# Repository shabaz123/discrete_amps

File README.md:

# Discrete Amps

This repository contains  discrete audio amplifier designs intended primarily for speech applications (speech bandwidth, not music).  

Each design includes:
- KiCad 10 Schematic and PCB files
- KiCad 10 SPICE Simulation Workbook
- Gerber files for fabrication  
- PDF schematic export and PCB screenshots for easy viewing without KiCad  

---

## Preamp K1

Designed by M. Kellett, this preamplifier is optimised for speech signals in HF receivers.

- **Gain:** ~28 dB  
- **Bandwidth (-3 dB):** ~150 Hz to 10 kHz (approximate)  
- **Use case:** Moderate gain front-end with relatively wide speech bandwidth  

### Schematic

### PCB Top

### PCB Underside

### PCB Render

---

## Preamp K2

Also designed by M. Kellett, this version provides higher gain and a slightly narrower bandwidth, making it suitable where additional amplification is required.

- **Gain:** ~45 dB  
- **Bandwidth (-3 dB):** ~100 Hz to 7 kHz (approximate)  
- **Use case:** Higher gain stage for weak signal amplification  

### Schematic

### PCB Top

### PCB Underside

### PCB Render

---

## Poweramp K1

Also designed by M. Kellett, this amplifier is a power stage, and it directly drives 8 ohm speakers, with low distortion (less than 0.5%) at 280 mW.

- **Gain:** ~27 dB  
- **Bandwidth (-3 dB):** ~50 Hz to 30 kHz (approximate)  
- **Use case:** Driving an 8-ohm speaker in a radio receiver  

### Schematic

### PCB Top

### PCB Underside

### PCB Render

---

## Diffamp S1

This is a difference amplifier, designed for input signals up to about 400 mV p-p. Note: this circuit has not been assembled yet, and may have instabilities. 

- **Gain:** ~10 dB  
- **Bandwidth (-3 dB):** ~30 Hz to 40 kHz (approximate)  
- **Use case:** Acting somewhat like a telephone hybrid, for a DIY intercom/field phone, to remove the local audio sound from the remotely received sound

Note: For higher gain (about 30 dB) and correspondingly lower maximum imput signals, make the following two changes:

1. Take the output from Q4 collector, rather than Q3 collector
2. Move C6 to Q4 collector instead of Q3 collector.

### Schematic

### PCB Top

### PCB Underside

### PCB Render

---

## Notes

These designs are intended for experimentation and adaptation.

All components are easy to source. 

For the 9V power connection, the PCB will accomodate any 2-pin screw terminal block with 3.5 to 5.08 mm pin pitch. 

For the audio input and output, an AliExpress stereo audio jack socket can be used (only the tip and the screen is used, the ring is not connected). Alternatively, the audio connections can be made with 0.1" pin headers (they will fit in the same footprint, as there are extra holes for that). 

The potentiometer can be ALPS RK097 series (available from AliExpress), it has pins at 2.5 mm pitch, and a body width of 10 mm.

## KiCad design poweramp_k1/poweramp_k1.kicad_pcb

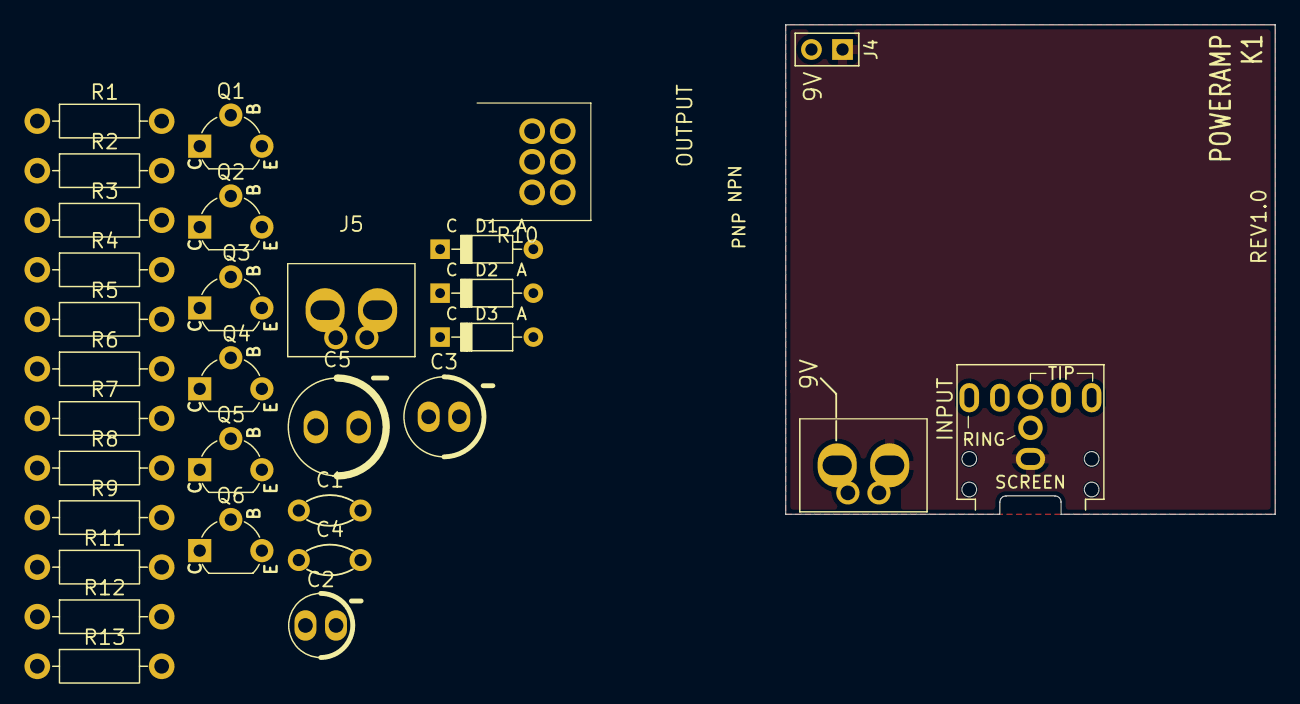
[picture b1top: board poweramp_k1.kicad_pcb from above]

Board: 2 copper layers, 40.0 x 40.0 mm, 31 parts (0 on the bottom side), 20 nets, no tracks yet.

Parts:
C1: 220n; C_Disc_T3.0mm_P5.0
C2: 10u; CP_Radial_D5.0mm_P2.50mm
C3: 47u; CP_Radial_D6.3mm_P2.50mm
C4: 270p; C_Disc_T3.0mm_P5.0
C5: 470u; CP_Radial_D8mm_P3.5mm
D1, D2, D3: 1N4148; Diode-DO-35_1.75mmDia_3.4mmWidth_P7.62mm
J1: AudioJack_Stereo; Jack_3.5mm_CUI_SJ1-3525N_Horizontal
J3: 9VDC; TerminalBlock_2way-3.5-5.0mm
J4: PinHeader_1x02_P2.54mm_Vertical
J5: SPEAKER; TerminalBlock_2way-3.5-5.0mm
Q1, Q5, Q6: BC547; BJT_NPN_BC547
Q2: BC337-25; BJT_NPN_BC547
Q3: BC557; BJT_PNP_BC557
Q4: BC327-25; BJT_PNP_BC557
R1, R2: 2.2R; R_Axial_L6.3mm_D2.5mm_P10.16mm_Horiz
R3: 10k; R_Axial_L6.3mm_D2.5mm_P10.16mm_Horiz
R4: 1.5k; R_Axial_L6.3mm_D2.5mm_P10.16mm_Horiz
R5: 1k; R_Axial_L6.3mm_D2.5mm_P10.16mm_Horiz
R6: 33k; R_Axial_L6.3mm_D2.5mm_P10.16mm_Horiz
R7: 150R; R_Axial_L6.3mm_D2.5mm_P10.16mm_Horiz
R8: 2k; R_Axial_L6.3mm_D2.5mm_P10.16mm_Horiz
R9: 22k; R_Axial_L6.3mm_D2.5mm_P10.16mm_Horiz
R10: 22k; Potentiometer_RD701F
R11: 630R; R_Axial_L6.3mm_D2.5mm_P10.16mm_Horiz
R12: 27k; R_Axial_L6.3mm_D2.5mm_P10.16mm_Horiz
R13: 43k; R_Axial_L6.3mm_D2.5mm_P10.16mm_Horiz

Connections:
0V: C2.2, C3.2, D3.1 (K), J1.S, J3.2, J4.1, J5.2, Q4.1 (C), R4.2, R7.2, R10.1, R13.2
/IN: J1.T, R10.3
/OUT: C5.2, J5.1
unnamed: C1.1, R10.2
unnamed: C2.1, R5.2
unnamed: C3.1, R3.2, R6.1
unnamed: C4.2, C5.1, R1.2, R2.1, R9.2
unnamed: D1.2 (A), Q2.2 (B), Q3.1 (C)
unnamed: D1.1 (K), D2.2 (A)
unnamed: D2.1 (K), Q4.2 (B), Q5.1 (C)
unnamed: D3.2 (A), R8.2
unnamed: C1.2, Q1.2 (B), R6.2, R13.1
unnamed: Q1.1 (C), Q3.2 (B), R11.2
unnamed: Q1.3 (E), Q6.3 (E), R4.1
unnamed: Q2.3 (E), R1.1
unnamed: Q4.3 (E), R2.2
unnamed: Q5.2 (B), R8.1, R12.2
unnamed: Q5.3 (E), R7.1
unnamed: C4.1, Q6.2 (B), R5.1, R9.1
V+: J3.1, J4.2, Q2.1 (C), Q3.3 (E), Q6.1 (C), R3.1, R11.1, R12.1

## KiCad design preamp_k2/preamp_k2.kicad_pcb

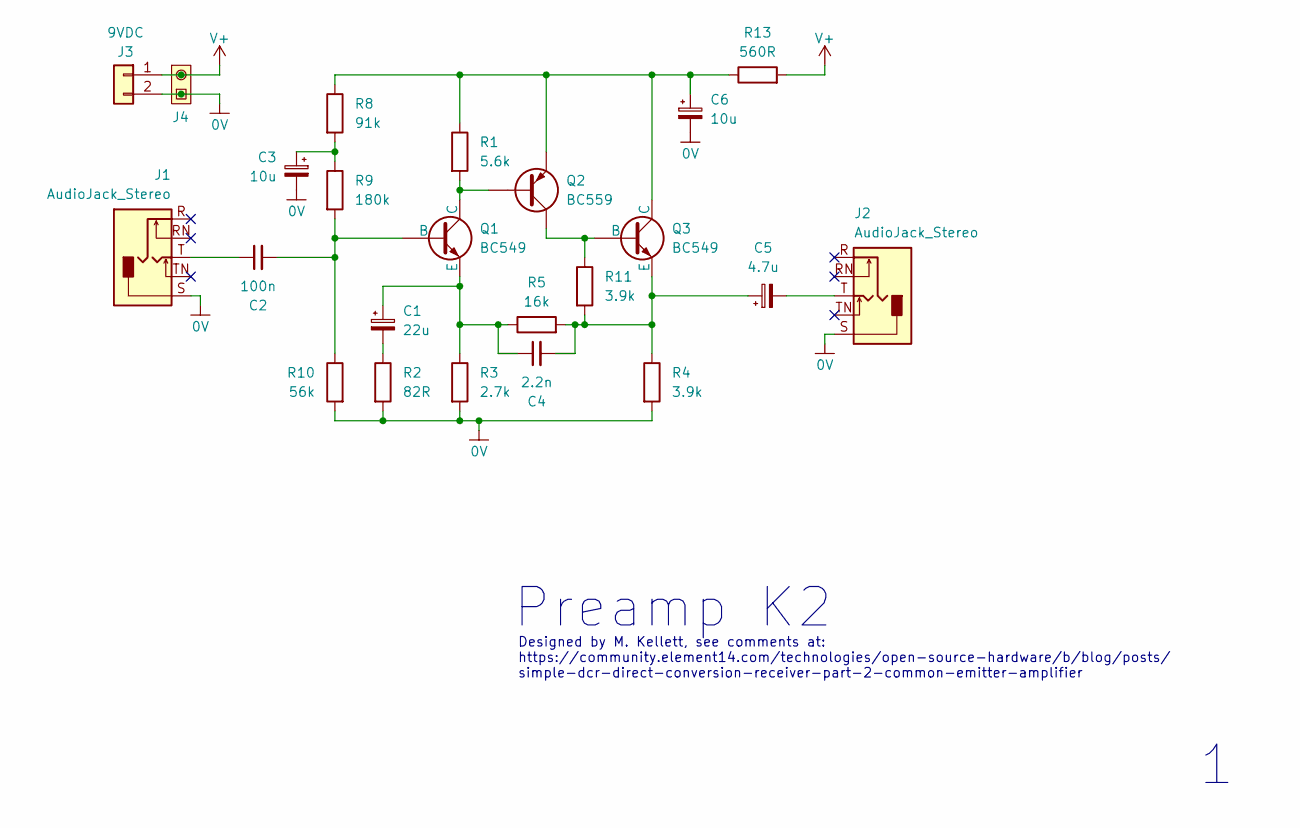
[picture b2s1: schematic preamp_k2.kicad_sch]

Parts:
C1: 22u; CP_Radial_D5.0mm_P2.50mm
C2: 100n; C_Disc_T3.0mm_P5.0
C3, C6: 10u; CP_Radial_D5.0mm_P2.50mm
C4: 2.2n; C_Disc_T3.0mm_P5.0
C5: 4.7u; CP_Radial_D5.0mm_P2.50mm
J1, J2: AudioJack_Stereo; Jack_3.5mm_CUI_SJ1-3525N_Horizontal
J3: 9VDC; TerminalBlock_2way-3.5-5.0mm
J4: PinHeader_1x02_P2.54mm_Vertical
Q1, Q3: BC549; BJT_NPN_BC547
Q2: BC559; BJT_PNP_BC557
R1: 5.6k; R_Axial_L6.3mm_D2.5mm_P10.16mm_Horiz
R2: 82R; R_Axial_L6.3mm_D2.5mm_P10.16mm_Horiz
R3: 2.7k; R_Axial_L6.3mm_D2.5mm_P10.16mm_Horiz
R4, R11: 3.9k; R_Axial_L6.3mm_D2.5mm_P10.16mm_Horiz
R5: 16k; R_Axial_L6.3mm_D2.5mm_P10.16mm_Horiz
R8: 91k; R_Axial_L6.3mm_D2.5mm_P10.16mm_Horiz
R9: 180k; R_Axial_L6.3mm_D2.5mm_P10.16mm_Horiz
R10: 56k; R_Axial_L6.3mm_D2.5mm_P10.16mm_Horiz
R13: 560R; R_Axial_L6.3mm_D2.5mm_P10.16mm_Horiz

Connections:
0V: C3.2, C6.2, J1.S, J2.S, J3.2, J4.1, R2.2, R3.2, R4.2, R10.2
unnamed: C1.2, R2.1
unnamed: C2.1, J1.T
unnamed: C3.1, R8.2, R9.1
unnamed: C5.2, J2.T
unnamed: C2.2, Q1.2 (B), R9.2, R10.1
unnamed: Q1.1 (C), Q2.2 (B), R1.2
unnamed: C1.1, C4.1, Q1.3 (E), R3.1, R5.1
unnamed: Q2.1 (C), Q3.2 (B), R11.1
unnamed: C6.1, Q2.3 (E), Q3.1 (C), R1.1, R8.1, R13.1
unnamed: C4.2, C5.1, Q3.3 (E), R4.1, R5.2, R11.2
V+: J3.1, J4.2, R13.2

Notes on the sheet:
Designed by M. Kellett, see comments at: https://community.element14.com/technologies/open-source-hardware/b/blog/posts/ simple-dcr-direct-conversion-receiver-part-2-common-emitter-amplifier
Preamp K2

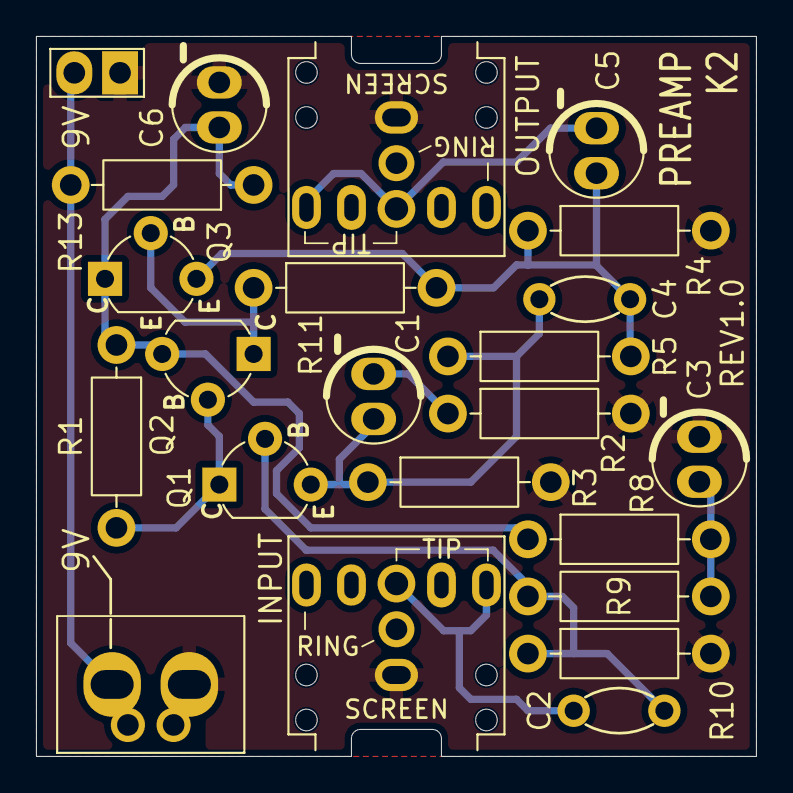
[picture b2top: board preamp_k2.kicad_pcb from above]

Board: 2 copper layers, 40.0 x 40.0 mm, 23 parts (0 on the bottom side), 12 nets.

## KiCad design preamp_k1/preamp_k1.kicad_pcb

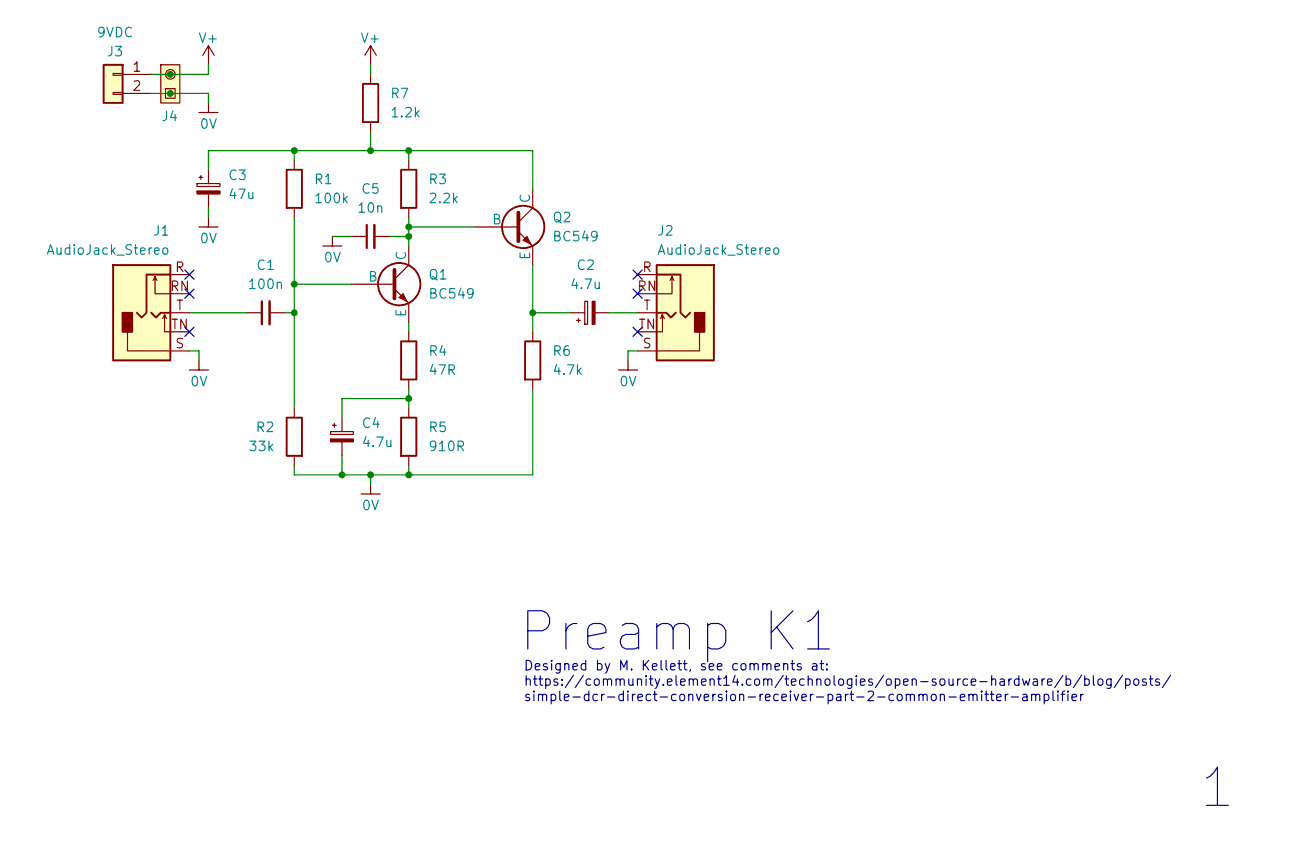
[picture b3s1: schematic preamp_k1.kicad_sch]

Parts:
C1: 100n; C_Disc_T3.0mm_P5.0
C2: 4.7u; CP_Radial_D5.0mm_P2.50mm
C3: 47u; CP_Radial_D6.3mm_P2.50mm
C4: 4.7u; CP_Radial_D6.3mm_P2.50mm
C5: 10n; C_Disc_T3.0mm_P5.0
J1, J2: AudioJack_Stereo; Jack_3.5mm_CUI_SJ1-3525N_Horizontal
J3: 9VDC; TerminalBlock_2way-3.5-5.0mm
J4: PinHeader_1x02_P2.54mm_Vertical
Q1, Q2: BC549; BJT_NPN_BC547
R1: 100k; R_Axial_L6.3mm_D2.5mm_P10.16mm_Horiz
R2: 33k; R_Axial_L6.3mm_D2.5mm_P10.16mm_Horiz
R3: 2.2k; R_Axial_L6.3mm_D2.5mm_P10.16mm_Horiz
R4: 47R; R_Axial_L6.3mm_D2.5mm_P10.16mm_Horiz
R5: 910R; R_Axial_L6.3mm_D2.5mm_P10.16mm_Horiz
R6: 4.7k; R_Axial_L6.3mm_D2.5mm_P10.16mm_Horiz
R7: 1.2k; R_Axial_L6.3mm_D2.5mm_P10.16mm_Horiz

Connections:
0V: C3.2, C4.2, C5.1, J1.S, J2.S, J3.2, J4.1, R2.2, R5.2, R6.2
unnamed: C1.1, J1.T
unnamed: C2.2, J2.T
unnamed: C4.1, R4.2, R5.1
unnamed: C1.2, Q1.2 (B), R1.2, R2.1
unnamed: C5.2, Q1.1 (C), Q2.2 (B), R3.2
unnamed: Q1.3 (E), R4.1
unnamed: C3.1, Q2.1 (C), R1.1, R3.1, R7.2
unnamed: C2.1, Q2.3 (E), R6.1
V+: J3.1, J4.2, R7.1

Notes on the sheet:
Designed by M. Kellett, see comments at: https://community.element14.com/technologies/open-source-hardware/b/blog/posts/ simple-dcr-direct-conversion-receiver-part-2-common-emitter-amplifier
Preamp K1

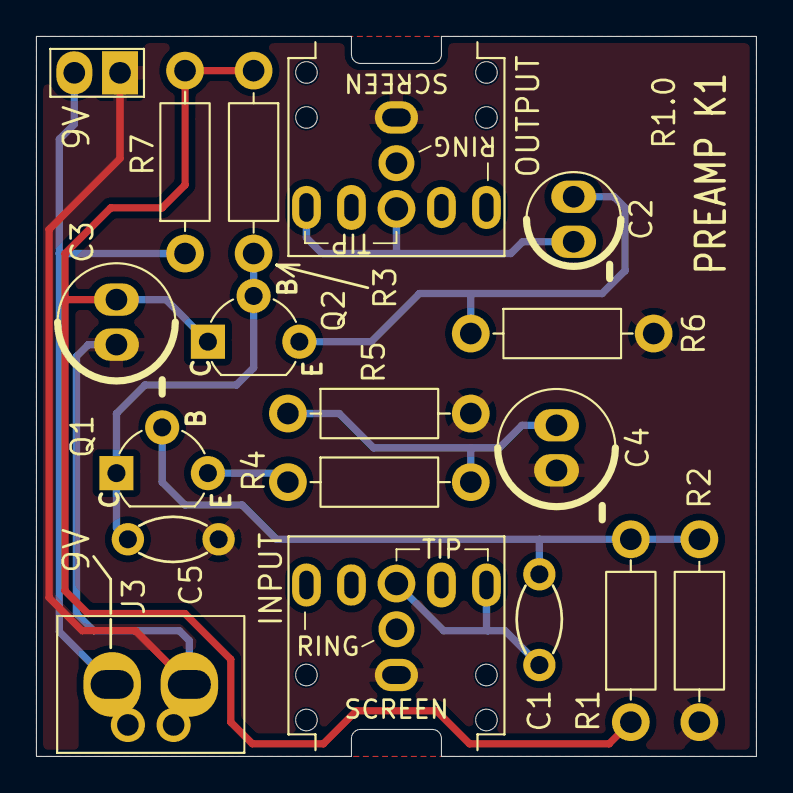
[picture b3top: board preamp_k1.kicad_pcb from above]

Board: 2 copper layers, 40.0 x 40.0 mm, 18 parts (0 on the bottom side), 10 nets.

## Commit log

2026-04-12 Enhance README with preamp design details
    Updated README to provide detailed descriptions of two discrete audio preamplifier designs, including specifications and images.
2026-04-12 Fix schematic image filename in README
2026-04-12 Fix typo in schematic image filename
2026-04-12 Update notes section with component sourcing details
    Added sourcing information for components and clarified PCB connections.
2026-04-15 Update README to clarify amplifier design description
2026-04-18 Clarify application focus in README
    Updated description to clarify application focus.
